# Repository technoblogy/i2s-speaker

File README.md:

# I2S Speaker for QT Py
An expansion board for QT Py microcontroller boards to provide a 3W stereo power amplifier output from the digital I2S output.

For more information see: http://www.technoblogy.com/show?4ECO.

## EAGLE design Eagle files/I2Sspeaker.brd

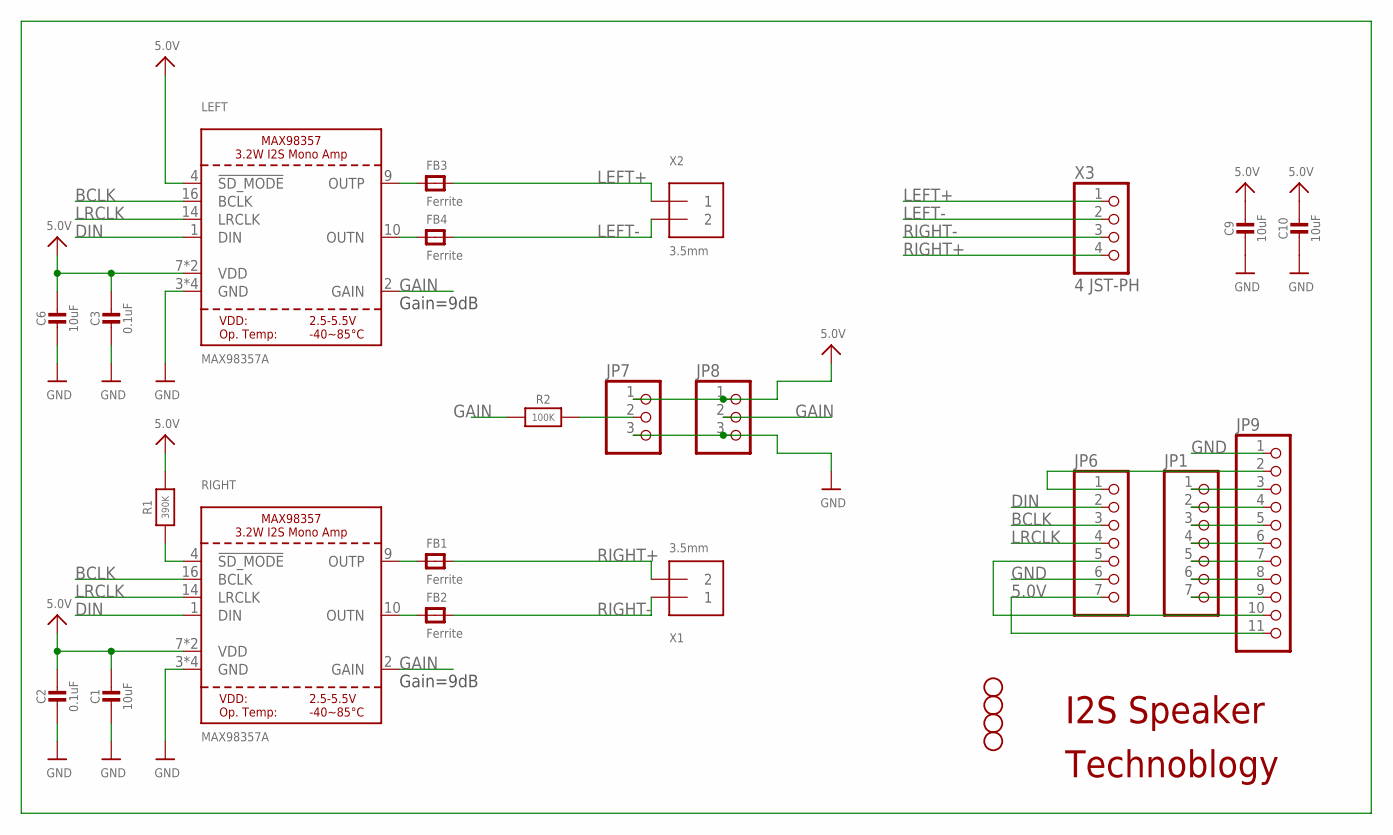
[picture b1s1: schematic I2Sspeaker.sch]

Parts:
C1, C6, C9, C10: 10uF; 0805-NO
C2, C3: 0.1uF; 0805-NO
FB1, FB2, FB3, FB4: Ferrite; 0805-NO
JP1, JP6: HEADER-1X7ROUND; 1X07_ROUND
JP2, JP3, JP4, JP5: STAND-OFF
JP7, JP8: HEADER-1X3ROUND; 1X03_ROUND
JP9: HEADER-1X11; 1X11_ROUND
LEFT: MAX98357A; QFN16_3MM
R1: 390K; 0805-NO
R2: 100K; 0805-NO
RIGHT: MAX98357A; QFN16_3MM
X1, X2: 3.5mm; TERMBLOCK_1X2-3.5MM
X3: 4 JST-PH; JSTPH4

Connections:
5.0V: C1.1, C2.1, C3.1, C6.1, C9.1, C10.1, JP6.7, JP7.1, JP8.1, JP9.11, LEFT.4 (!SD_MODE), LEFT.7 (VDD), LEFT.8 (VDD), R1.2, RIGHT.7 (VDD), RIGHT.8 (VDD)
BCLK: JP6.3, LEFT.16 (BCLK), RIGHT.16 (BCLK)
DIN: JP6.2, LEFT.1 (DIN), RIGHT.1 (DIN)
GAIN: JP8.2, LEFT.2 (GAIN), R2.1, RIGHT.2 (GAIN)
GND: C1.2, C2.2, C3.2, C6.2, C9.2, C10.2, JP6.6, JP7.3, JP8.3, JP9.1, LEFT.3 (GND), LEFT.11 (GND), LEFT.15 (GND), LEFT.THERMAL (GND), RIGHT.3 (GND), RIGHT.11 (GND), RIGHT.15 (GND), RIGHT.THERMAL (GND)
LEFT+: FB3.2, X2.1, X3.1
LEFT-: FB4.2, X2.2, X3.2
LRCLK: JP6.4, LEFT.14 (LRCLK), RIGHT.14 (LRCLK)
unnamed: FB4.1, LEFT.10 (OUTN)
unnamed: FB3.1, LEFT.9 (OUTP)
unnamed: FB2.1, RIGHT.10 (OUTN)
unnamed: FB1.1, RIGHT.9 (OUTP)
unnamed: JP1.1, JP9.3
unnamed: JP6.5, JP9.10
unnamed: JP7.2, R2.2
unnamed: JP1.2, JP9.4
unnamed: JP1.3, JP9.5
unnamed: JP1.4, JP9.6
unnamed: JP1.5, JP9.7
unnamed: JP1.6, JP9.8
unnamed: JP1.7, JP9.9
unnamed: JP6.1, JP9.2
RIGHT+: FB1.2, X1.2, X3.4
RIGHT-: FB2.2, X1.1, X3.3
SD_MODE: R1.1, RIGHT.4 (!SD_MODE)

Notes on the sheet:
Gain=9dB
I2S Speaker
Technoblogy

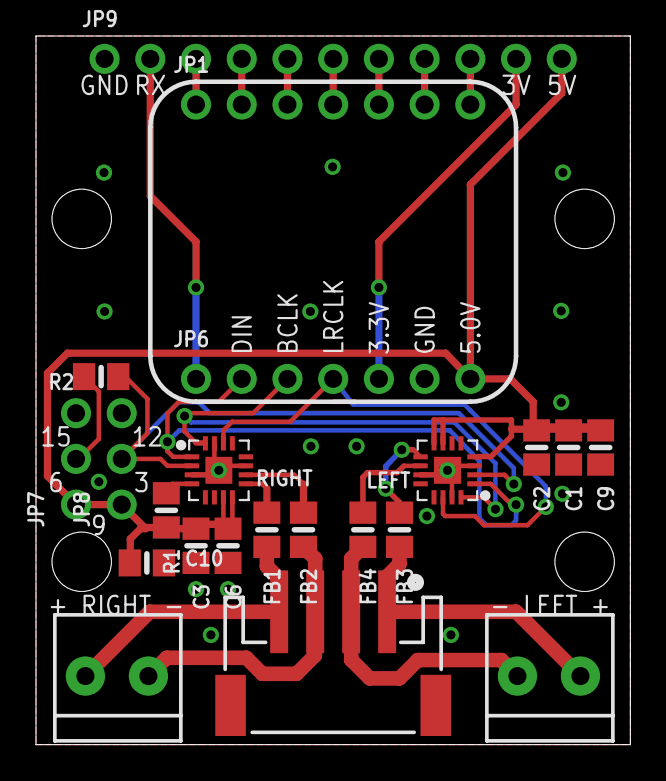
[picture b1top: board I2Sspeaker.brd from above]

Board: 2 copper layers, 33.0 x 39.4 mm, 26 parts (0 on the bottom side), 25 nets.

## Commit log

2023-04-27 Version 1 - 27th April 2023

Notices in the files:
parts and their libraries:
microbuilder: This work is placed in the public domain, and may be freely used for commercial and non-commercial work with the following conditions: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
